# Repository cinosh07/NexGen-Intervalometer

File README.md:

# NexGen Intervalometer

In this repo you will find the PCB for the intervalometer and 3D print files for the case. 

For the firmware please check link below. The firmware is a part of a camera slider project. This firmware has been develop with polymorphism in mind. So it can be used with a variety of hardware, including this standalone intervalometer. This is configured in the JSON config file that the firmware load at boot.

The firmware is availlable HERE https://github.com/cinosh07/ESP32_Camera_Slider

The interface is accessed by connecting to the Intervalometer hotspot over your mobile web browser. 

**Soon to come:**

**Optional OLED Display with rotary nob to be able to do configurations and operations without using the wireless application.**

To follow the project check out my youtube channel https://youtube.com/@carltremblay

**Here's the intervalometer with the optional flash shoe mount cover.**

# Features
- Easy to use HTML5 interface
- Designed for professionnal timelapse creator
- WIFI hot spot
- Real Time Clock (RTC) 10 ms accuracy over 1 year.
- Holy Grail Ramping
- Precise scheduling start with calendar
- Precise scheduling ramping with calendar
- You can pre-program your session at home and just plug it at location. Thanks to its RTC clock, it will start by itself at the right time. Just leave it and forget.
- Up to 25 shooting profiles that you can manage, rename and configure.
- 0.1 seconds steps
- Bulb Mode
- Easy to follow Interval Timeline display (at the top of the application) that help notice in a snap any conflict in configurations (i.e. Interval shorter than the minimun length require)
- Firmwate update via the web application  
- Camera Sentinel (to keep camera awake)
- Work in cold condition
- Work with Nikon, Canon, Fuji and Sony DSLR Cameras
- Built-in Li-Ion 2100 mAh battery (24 hours autonomy)
- Internal charger (charge in 3 hours @ 1amp)
- Can be powered with power supply for long terme use.
- Dimension: 62mm x 45mm x 45mm
- Dimension: 62mm x 61mm x 45mm (with optional flash hot shoe)
- Weight: < 100g
- And lot more ...

**Web application screenshot**

**RTC Clock view**

**Other side view**

**Inside the intervalometer**

**The PCB**

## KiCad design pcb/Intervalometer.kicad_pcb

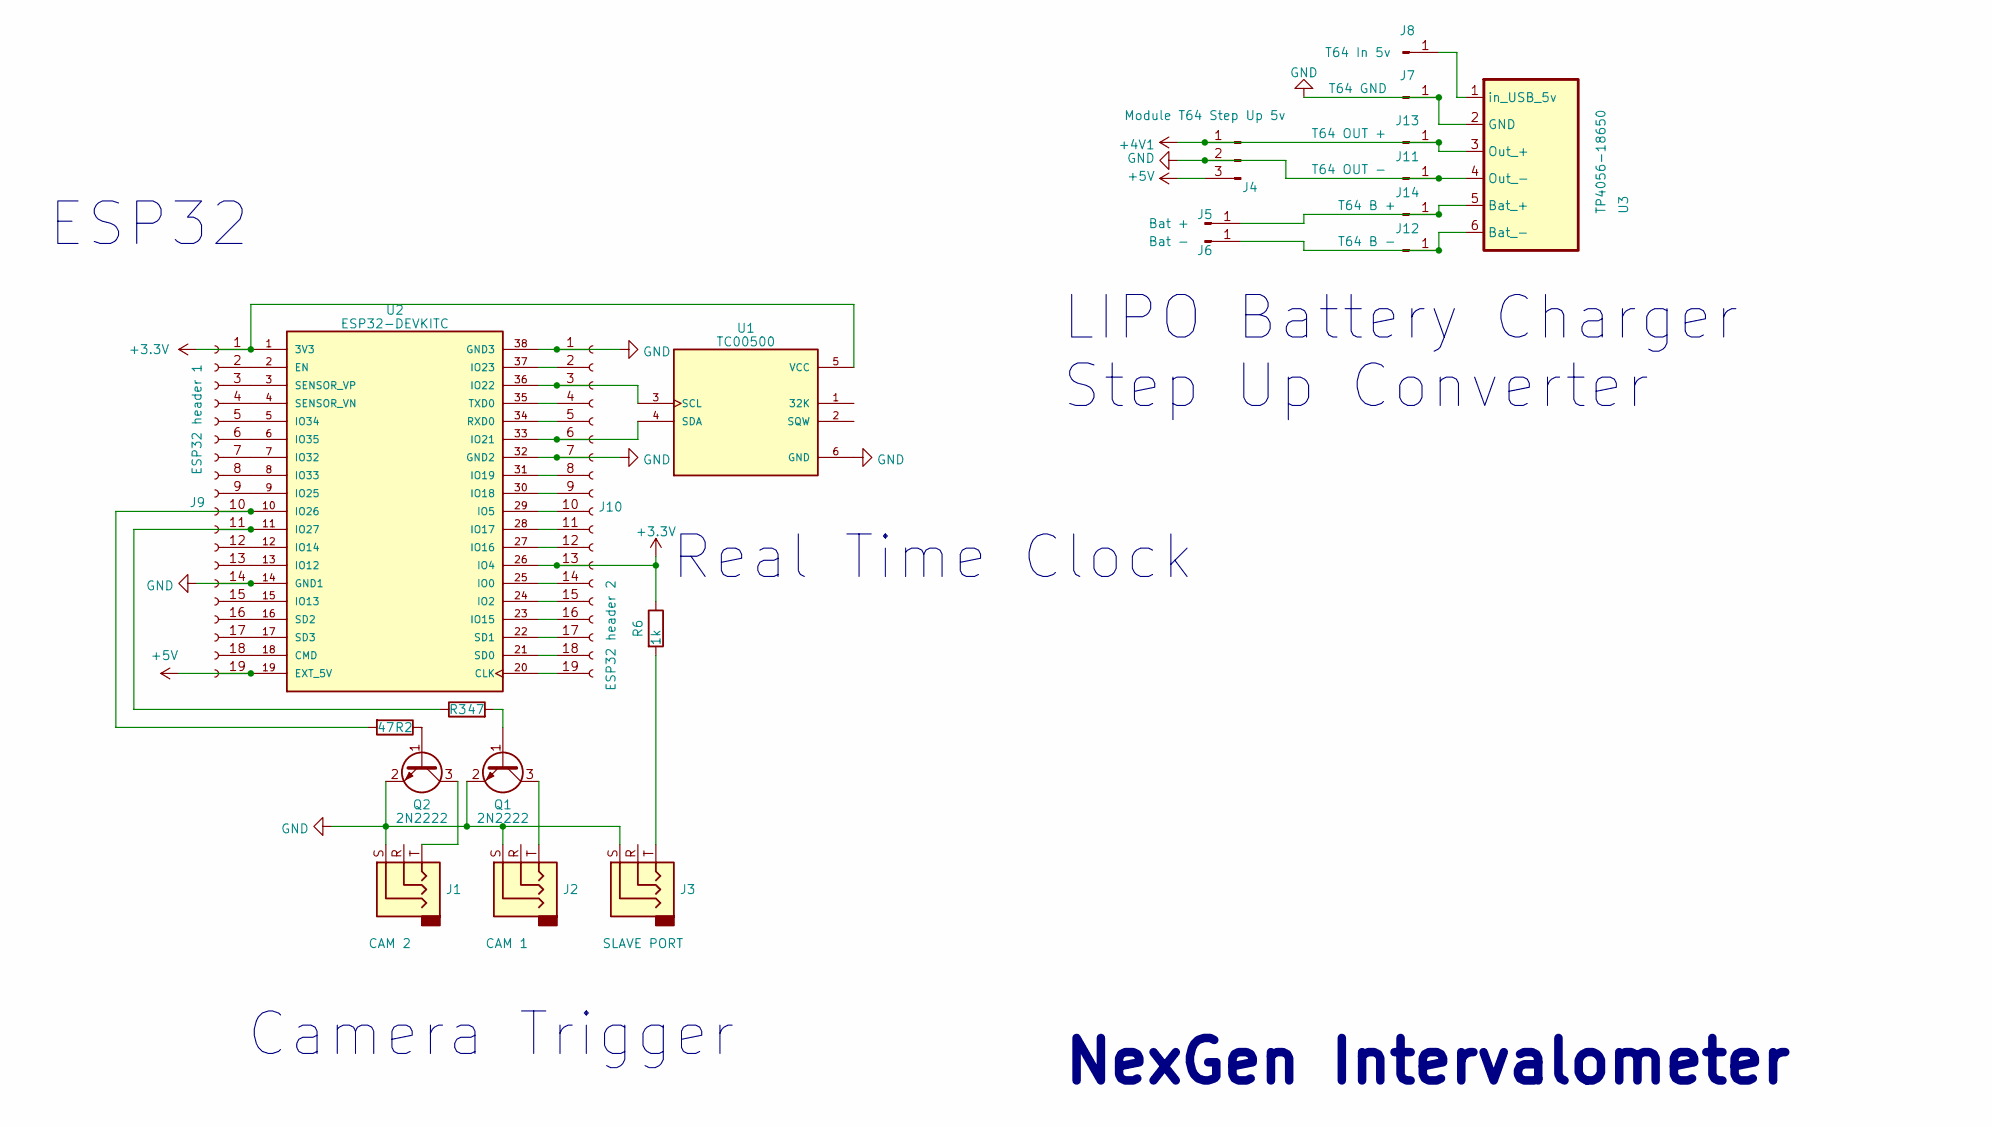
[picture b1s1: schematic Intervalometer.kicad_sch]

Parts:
J1: CAM 2; Jack_2.5mm_PJ208_Horizontal_CircularHoles
J2: CAM 1; Jack_2.5mm_PJ208_Horizontal_CircularHoles
J3: SLAVE PORT; Jack_2.5mm_PJ208_Horizontal_CircularHoles
J4: Module T64 Step Up 5v; PinHeader_1x03_P2.54mm_Vertical
J5: Bat +; Pin_D1.0mm_L10.0mm_LooseFit
J6: Bat -; Pin_D1.0mm_L10.0mm_LooseFit
J7: T64 GND; PinHeader_1x01_P2.54mm_Vertical
J8: T64 In 5v; PinHeader_1x01_P2.54mm_Vertical
J9: ESP32 header 1; PinSocket_1x19_P2.54mm_Vertical
J10: ESP32 header 2; PinSocket_1x19_P2.54mm_Vertical
J11: T64 OUT -; PinHeader_1x01_P2.54mm_Vertical
J12: T64 B -; PinHeader_1x01_P2.54mm_Vertical
J13: T64 OUT +; PinHeader_1x01_P2.54mm_Vertical
J14: T64 B +; PinHeader_1x01_P2.54mm_Vertical
Q1, Q2: 2N2222; SOT-23
R2, R3: 47; R_0805_2012Metric
R6: 1k; R_0805_2012Metric
U1: TC00500; MODULE_TC00500; PARTREV N/A
U2: ESP32-DEVKITC; MODULE_ESP32-DEVKITC; PARTREV N/A
U3: TP4056-18650

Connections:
+3.3V: J9.1, J10.13, R6.1, U1.5 (VCC), U2.1 (3V3), U2.26 (IO4)
+4V: J4.1, J13.1, U3.3 (Out_+)
+5V: J4.3, J9.19, U2.19 (EXT_5V)
GND: J1.S, J2.S, J3.S, J4.2, J7.1, J9.14, J10.1, J10.7, J11.1, Q1.2 (E), Q2.2 (E), U1.6 (GND), U2.14 (GND1), U2.32 (GND2), U2.38 (GND3), U3.2 (GND), U3.4 (Out_-)
unnamed: J3.T, R6.2
unnamed: J8.1, U3.1 (in_USB_5v)
unnamed: J9.2, U2.2 (EN)
unnamed: J9.3, U2.3 (SENSOR_VP)
unnamed: J9.4, U2.4 (SENSOR_VN)
unnamed: J9.5, U2.5 (IO34)
unnamed: J9.6, U2.6 (IO35)
unnamed: J9.7, U2.7 (IO32)
unnamed: J9.8, U2.8 (IO33)
unnamed: J9.9, U2.9 (IO25)
unnamed: J9.10, R2.2, U2.10 (IO26)
unnamed: J9.11, R3.1, U2.11 (IO27)
unnamed: J9.12, U2.12 (IO14)
unnamed: J9.13, U2.13 (IO12)
unnamed: J9.15, U2.15 (IO13)
unnamed: J9.16, U2.16 (SD2)
unnamed: J9.17, U2.17 (SD3)
unnamed: J9.18, U2.18 (CMD)
unnamed: J10.2, U2.37 (IO23)
unnamed: J10.3, U1.3 (SCL), U2.36 (IO22)
unnamed: J10.4, U2.35 (TXD0)
unnamed: J10.5, U2.34 (RXD0)
unnamed: J10.6, U1.4 (SDA), U2.33 (IO21)
unnamed: J10.8, U2.31 (IO19)
unnamed: J10.9, U2.30 (IO18)
unnamed: J10.10, U2.29 (IO5)
unnamed: J10.11, U2.28 (IO17)
unnamed: J10.12, U2.27 (IO16)
unnamed: J10.14, U2.25 (IO0)
unnamed: J10.15, U2.24 (IO2)
unnamed: J10.16, U2.23 (IO15)
unnamed: J10.17, U2.22 (SD1)
unnamed: J10.18, U2.21 (SD0)
unnamed: J10.19, U2.20 (CLK)
unnamed: J6.1, J12.1, U3.6 (Bat_-)
unnamed: J5.1, J14.1, U3.5 (Bat_+)
unnamed: Q1.1 (B), R3.2
unnamed: J2.T, Q1.3 (C)
unnamed: Q2.1 (B), R2.1
unnamed: J1.T, Q2.3 (C)

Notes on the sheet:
Camera Trigger
NexGen Intervalometer
Real Time Clock
LIPO Battery Charger Step Up Converter
ESP32

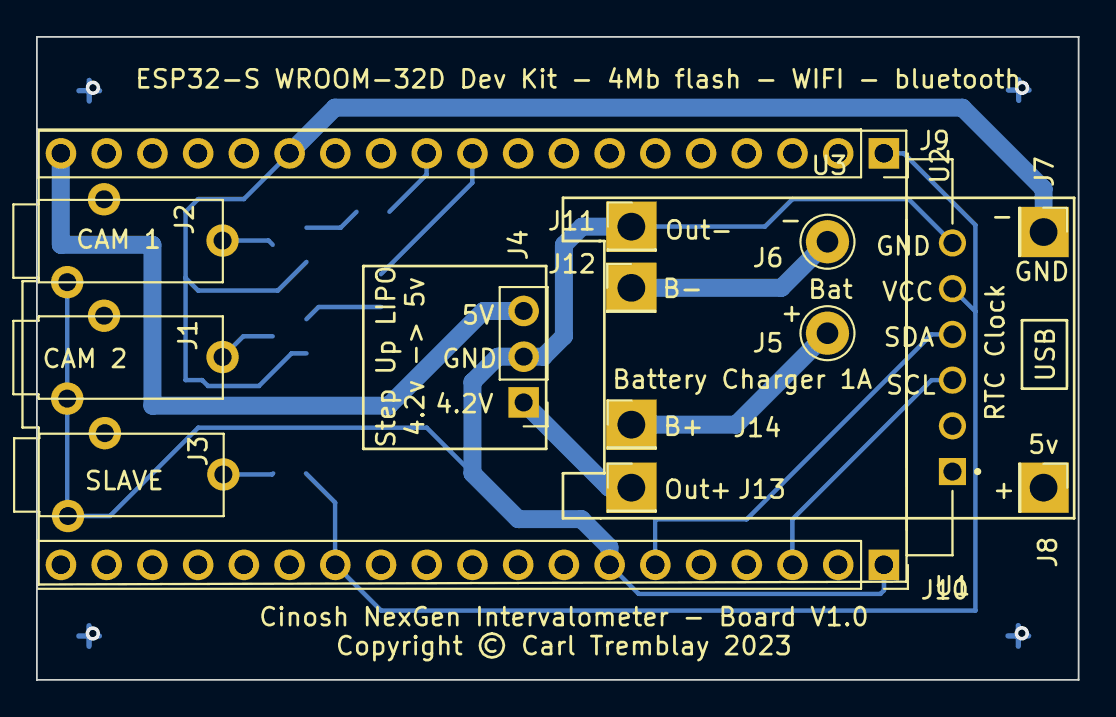
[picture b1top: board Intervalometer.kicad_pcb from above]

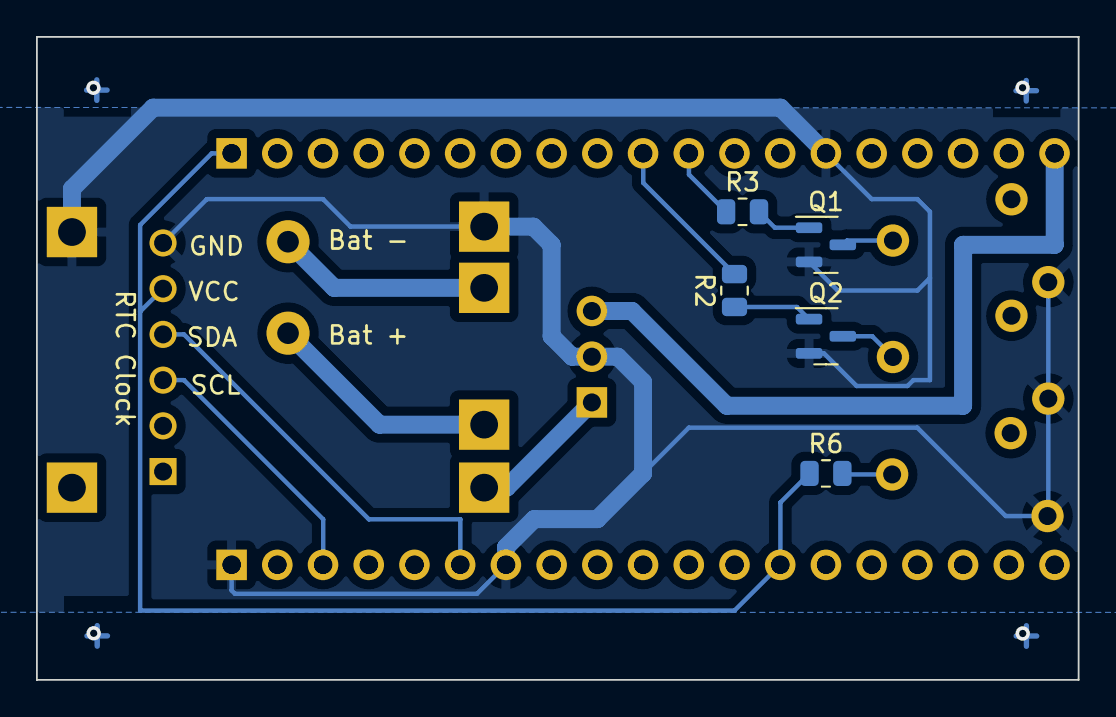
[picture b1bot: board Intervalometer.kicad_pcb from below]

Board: 2 copper layers, 57.9 x 35.7 mm, 22 parts (5 on the bottom side), 44 nets.

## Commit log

2023-03-11 modif
2023-03-11 resize images
2023-03-11 modifs
2023-03-12 Ajout au readme
2023-03-12 3d print files
2023-03-13 Modif grandeurs stl

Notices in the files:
pcb/Intervalometer.kicad_pcb:
Copyright © Carl Tremblay 2023
